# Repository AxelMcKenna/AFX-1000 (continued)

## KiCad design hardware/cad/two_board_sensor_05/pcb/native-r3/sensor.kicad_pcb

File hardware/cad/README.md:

# Enclosure and control CAD

Current completion work adds [BPM/selector carriers and breakout boards](two_board_controls_04/README.md),
a [sensor carrier and spring assembly](two_board_sensor_05/README.md), and an
[external fan-pod alternative](two_board_installation_06/README.md).
[Combined addon checks](two_board_integrated_07/README.md) pass for the recorded
source snapshot. These are development additions; complete LED/harness/sensor
PCB integration and physical/thermal acceptance remain open. They do not
silently replace the sealed r6 print package below.

Start with the [print-first kit](two_board_print_02/TBH01-r6-print-first-kit.zip) and [minimum print list](two_board_print_02/README.md). Its small core-coupon layout checks the critical fits before the full case print; the sealed r6 housing geometry is unchanged.

## Current two-board print package

Use [TBH01 print instructions and files](two_board_print_01/README.md) for the current two-board housing. It includes one-piece and split shell, lid, rear plate and guide exports, current PCB supports, captive lid fasteners, joining hardware and fit coupons. The body is 338 × 192.4 × 45.6 mm; the largest split shell footprint is 175 × 192.4 mm before adding a brim.

The current geometry is for an **unpowered physical fit prototype**. Selector, display/LED and angle-sensor carriers remain unfinished. Printer/material settings, actual hardware tolerances, complete wiring and operational cooling still require verification. Mesh integrity and modeled clearance checks do not establish electrical or thermal readiness.

## Current lever retention add-on

Use the [TBH03-r5 lever retention ZIP](two_board_print_03/TBH03-lever-retention-r5.zip) and [assembly/print instructions](two_board_print_03/README.md) with the r6 housing. Its replacement bracket and removable right-bearing cap resolve rigid arm insertion and positively retain the steel pivot. Use this bracket instead of the original r6 lever bracket; the r6 housing and arm remain unchanged.

Print the small pivot coupon first, then the bracket, cap and selected left/right thrust shims. The default pair is 0.9 mm, accepted only after measuring free endplay. The largest add-on part is 49 × 17 mm before brim. The package includes exact hardware specifications, a demonstrated horizontal assembly sequence, editable sources and [independent verification](two_board_print_03/independent-review.json): 14 valid delivery meshes, 15 empty clearance/path checks and four positive retention/stop checks. This completes the modeled lever retention for the unpowered fit prototype; the other carrier and operational qualifications above remain open.

## Earlier A07 design

The files below retain the earlier standalone housing, lever mechanism, control layout and component reserves. A07 reads the output, input-hub, processor-carrier, LED-driver and E23 power-input placement records. Its historical checks do not qualify the current two-board housing; see the current package above and the [validation record](../validation/README.md).

### Earlier files

| Location | Purpose |
| --- | --- |
| `enclosure.scad` | Housing, panel, rear plate, mounts and assembly views |
| `mechanisms.scad` | Lever, touch backer and fit coupon |
| `generate.py` | Control coordinates, apertures and parameter schedule |
| `standalone.py` | Board/component reserves, fixing bounds and rear I/O |
| `input_power.py` | Actual E23 profile/footprints, inlet/switch bounds and rear-panel alignment |
| `render.py` | Mechanical exports, mesh/motion checks and preview generation |
| `button_fixture.scad`, `button_fixture.py`, `button_render.py` | [Button-fit fixture](BUTTON-FIT.md) |
| `generated/*.scad`, `*.svg`, `controls.csv` | Small generated coordinates and review drawings |
| `generated/*validation.json`, `internal-clearance.json` | Verification records |
| `../../build/artifacts/cad/` | Ignored STL, DXF and PNG exports |
| `../../docs/assets/hardware/` | Selected, tracked documentation previews |

The [dated CAD design notes](../../docs/hardware/history/2026-10-23-cad-design.md) retain dimensions, allowances and the earlier placement discussion. Component investigations live in [research](../../research/hardware/components.md). Review ZIPs are listed in the [release catalog](../releases/README.md).

## Earlier A07 regeneration

Run from the repository root with the [uv environment](../../README.md#python-tooling), KiCad and OpenSCAD installed:

```sh
uv sync --locked
uv run --locked python -m hardware.cad.generate
uv run --locked python -m hardware.electronics.output_stage.generate
uv run --locked python -m hardware.electronics.output_stage.place --kicad-cli /path/to/kicad-cli
uv run --locked python -m hardware.electronics.output_stage.route
uv run --locked python -m hardware.electronics.output_stage.check_placement --kicad-cli /path/to/kicad-cli
uv run --locked python -m hardware.electronics.control_inputs.generate
uv run --locked python -m hardware.electronics.control_inputs.board --kicad-cli /path/to/kicad-cli
uv run --locked python -m hardware.electronics.processor_carrier.generate
uv run --locked python -m hardware.electronics.processor_carrier.board --kicad-cli /path/to/kicad-cli
uv run --locked python -m hardware.electronics.processor_carrier.verify --kicad-cli /path/to/kicad-cli
uv run --locked python -m hardware.electronics.control_inputs.verify --kicad-cli /path/to/kicad-cli
uv run --locked python -m hardware.electronics.led_driver.generate
uv run --locked python -m hardware.electronics.led_driver.place --kicad-cli /path/to/kicad-cli
uv run --locked python -m hardware.electronics.led_driver.route
uv run --locked python -m hardware.electronics.led_driver.cleanup --kicad-cli /path/to/kicad-cli
uv run --locked python -m hardware.electronics.input_protection.generate
uv run --locked python -m hardware.electronics.input_protection.place --kicad-cli /path/to/kicad-cli
uv run --locked python -m hardware.electronics.input_protection.route
uv run --locked python -m hardware.electronics.input_protection.cleanup --kicad-cli /path/to/kicad-cli
uv run --locked python -m hardware.electronics.input_protection.check_board --kicad-cli /path/to/kicad-cli
uv run --locked python -m hardware.electronics.power_supply.verify --kicad-cli /path/to/kicad-cli
uv run --locked python -m hardware.electronics.input_protection.verify --kicad-cli /path/to/kicad-cli
uv run --locked python -m hardware.electronics.rail_disconnect.verify --kicad-cli /path/to/kicad-cli
uv run --locked python -m hardware.electronics.led_driver.verify --kicad-cli /path/to/kicad-cli
uv run --locked python -m hardware.cad.standalone
uv run --locked python -m hardware.cad.render --openscad /path/to/openscad
```

Refresh `power_supply`, `input_protection` and `rail_disconnect` verification in
that order before E20 verification when their source fingerprints differ. The
[E20 guide](../electronics/led_driver/README.md) records its unclosed power
allocation and unfinished front-panel emitters/harnesses. The housing includes
four E20 M2 insert bosses and conditional component/tail/harness envelopes;
those bounds do not qualify selected parts or physical assembly.

A07 adds four input-board M2 insert bosses, profile reliefs around the rear web
and output-stage parts, a rectangular jack-body aperture and a lower power-switch
slot. The nominal jack face reaches the rear plate outer plane. The native input
collision check includes the rear plate and the complete allocated actuator sweep.
Plug mating, switch access/feel, exact part tolerances, insert/screw selection and
physical fit remain unqualified. Main rail-generation/disconnect PCBs and complete
analog/control placement still do not fit by inference from the generic power reserve.

Meshes and previews are written to `build/artifacts/cad/`; small verification records remain in `hardware/cad/generated/`. Add `--update-previews` to copy the selected PNGs into the tracked documentation after a successful render. The button renderer supports the same option. Documentation previews represent their last reviewed snapshot.

The rendering checks require the OpenSCAD backends used by the model. Their recorded scope and version are in the generated validation JSON. Mesh closure, clearances and source-level checks remain separate from a physical print or full-unit fit test.

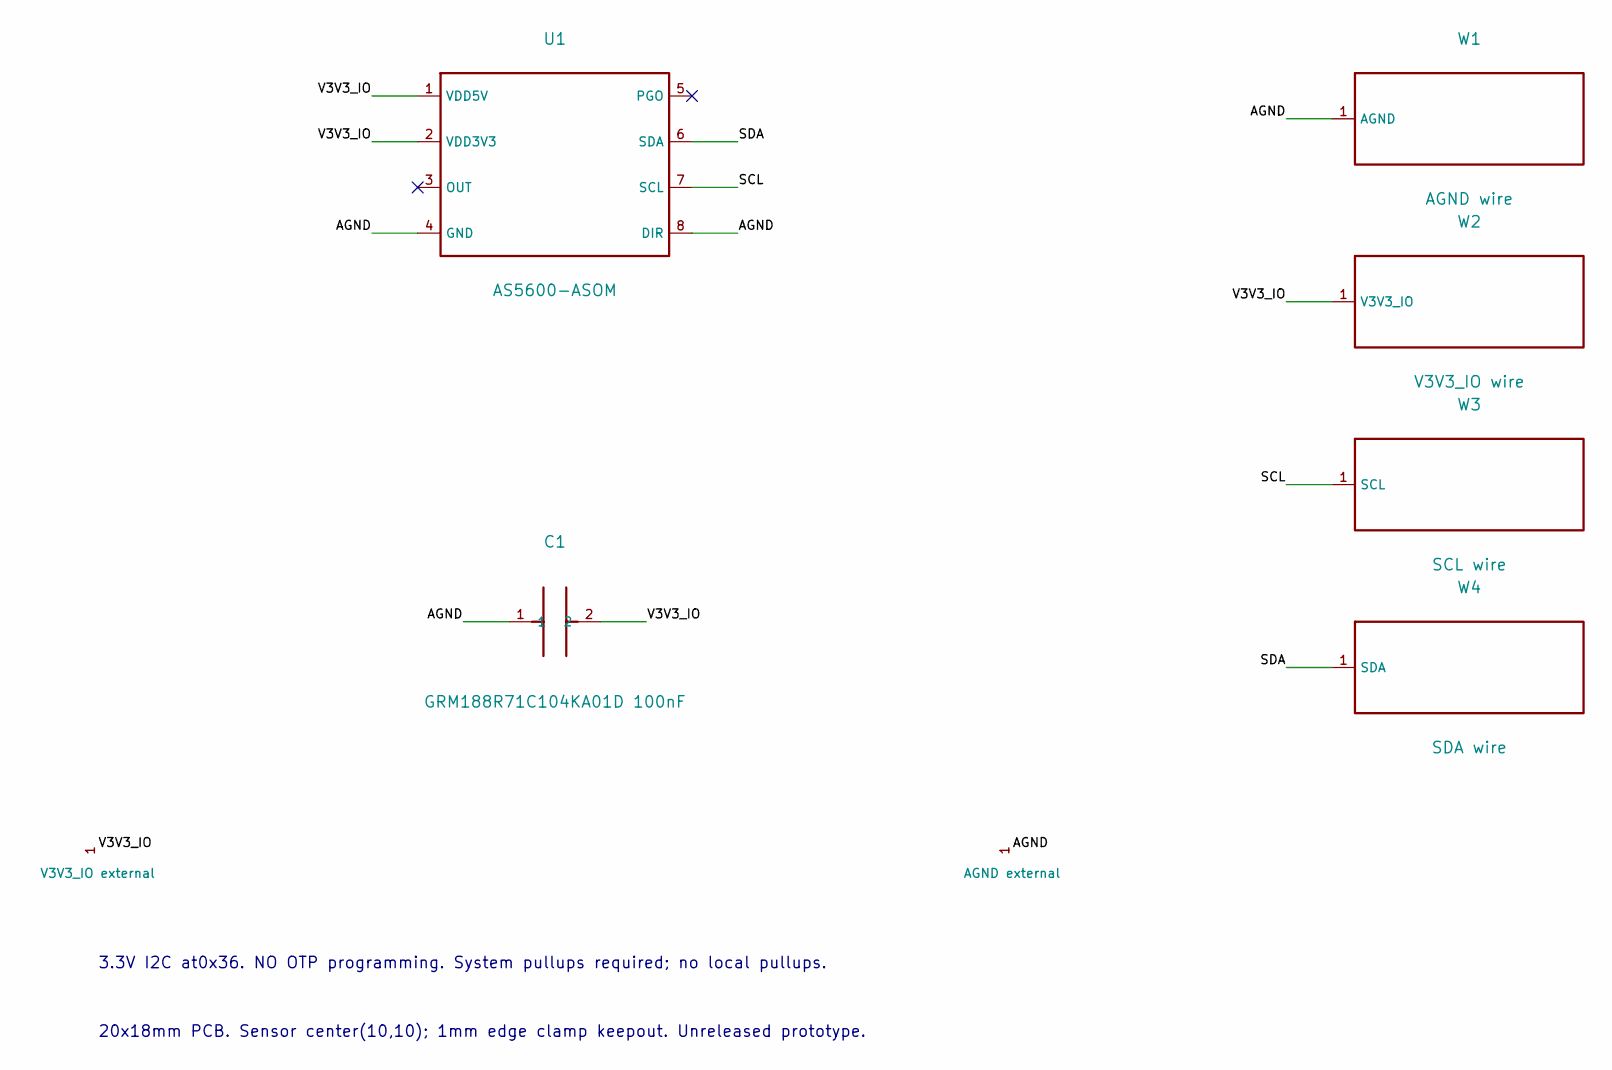
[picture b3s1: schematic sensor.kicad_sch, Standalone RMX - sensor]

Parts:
C1: GRM188R71C104KA01D 100nF; C0603
U1: AS5600-ASOM; SOIC8_3.9x4.9_P1.27
W1: AGND wire; WirePad
W2: V3V3_IO wire; WirePad
W3: SCL wire; WirePad
W4: SDA wire; WirePad

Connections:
/AGND: C1.1, U1.4 (GND), U1.8 (DIR), W1.1
/SCL: U1.7 (SCL), W3.1
/SDA: U1.6 (SDA), W4.1
/V3V3_IO: C1.2, U1.1 (VDD5V), U1.2 (VDD3V3), W2.1

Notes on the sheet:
3.3V I2C at0x36. NO OTP programming. System pullups required; no local pullups.
20x18mm PCB. Sensor center(10,10); 1mm edge clamp keepout. Unreleased prototype.

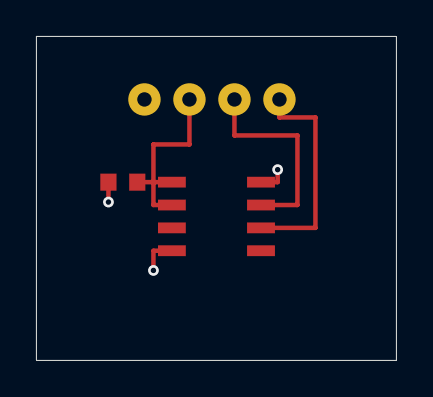
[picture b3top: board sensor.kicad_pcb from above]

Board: 2 copper layers, 20.0 x 18.0 mm, 6 parts (0 on the bottom side), 4 nets.

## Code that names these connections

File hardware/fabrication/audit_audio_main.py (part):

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          "PROC_IN_L","PROC_IN_R","PRE_OUT_L","PRE_OUT_R","RECV_L","RECV_R","PROC_OUT_L","PROC_OUT_R","GAIN_LOW"}
PORTS = {
    "J701": dict(value="43045-0600",footprint="Connector_Molex:Molex_Micro-Fit_3.0_43045-0600_2x03_P3.00mm_Horizontal",
                 pins=dict(zip(map(str,range(1,7)),("P19","AGND","N19","P12","N12","V5_REG")))),
    "J702": dict(value="B2B-XH-A(LF)(SN)",footprint="Connector_JST:JST_XH_B2B-XH-A_1x02_P2.50mm_Vertical",
                 pins={"1":"5V_DIG","2":"AGND"}),
}


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        assert pins[ref]["1"]=="5V_DIG", ("Coil on wrong 5V rail",ref)
    headers = {r:v for r,v in pins.items() if r.startswith("J")}
    assert set(headers)=={"J203","J402","J403","J602","J603","J606","J607","J608","J701","J702"}
    assert not any(net in {"CHIP_EN","ADC_DRV_ENABLE","ADC/PD_GATED",*ADC_STARS,*DAC_PINS,
                          "PROC_IN_L","PROC_IN_R","PRE_OUT_L","PRE_OUT_R","RECV_L","RECV_R","PROC_OUT_L","PROC_OUT_R","GAIN_LOW"}
                   for terminal in headers.values() for net in terminal.values()), "An internal audio/control boundary still has a header"
    assert [r for r in parts if not parts[r].findtext("footprint")]==["U201"]
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    def add(bundle,header,pin,role,peer,pin2,net):
        rows.append(dict(bundle=bundle,audio_header=header,audio_pin=str(pin),peer_role=role,
                         peer_header=peer,peer_pin=str(pin2),net=net))
    for pin,net in enumerate(("P19","AGND","N19","P12","N12","V5_REG"),1):
        add("ANALOG-POWER","J701",pin,"rail_disconnect","J3",pin,net)
    for pin,net in enumerate(("5V_DIG","AGND"),1):
        add("COIL-POWER","J702",pin,"rail_disconnect","J4",pin,net)
    for header,peer,nets,bundle in (
        ("J402","J1006",("AGND","V3V3_IO","SCL","SDA","CODEC_RUN","ANALOG_OK"),"MCU-CONTROL"),
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    ):
        for pin,net in enumerate(nets,1):
            add(bundle,header,pin,"digital_core",peer,pin,net)
    for pin,peer,net in ((7,1,"AGND"),(8,2,"PRE_ANALOG_OK")):
        add("RAIL-HEALTH","J402",pin,"rail_monitor","J4",peer,net)
    for pin,net in enumerate(("AGND","NBIAS_L","NBIAS_R"),1):
        add("BIAS-SENSE","J403",pin,"rail_monitor","J3",pin,net)
    for header,component,nets,bundle in (("J607","line_input",("IN_L","AGND","IN_R"),"REAR-IN"),
                                       ("J608","line_output",("OUT_L","AGND","OUT_R"),"REAR-OUT")):
        for pin,terminal,net in zip((1,2,3),("left","return","right"),nets):
            add(bundle,header,pin,"panel",component,terminal,net)
    for pin,terminal,net in ((1,"loop_supply","V3V3_IO"),(2,"process_loop","PROCESS_OK"),
                             (4,"sense_return","AGND"),(5,"sense","BYPASS_SENSE")):
        add("MANUAL-BYPASS","J603",pin,"panel","manual_bypass",terminal,net)
    return rows
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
